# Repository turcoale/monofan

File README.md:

# monofan
PCB de control Fan Monofásico

En este repositorio tengo el control de velocidad de FAN Monofásico.
Fecha de comienzo 23/11/15

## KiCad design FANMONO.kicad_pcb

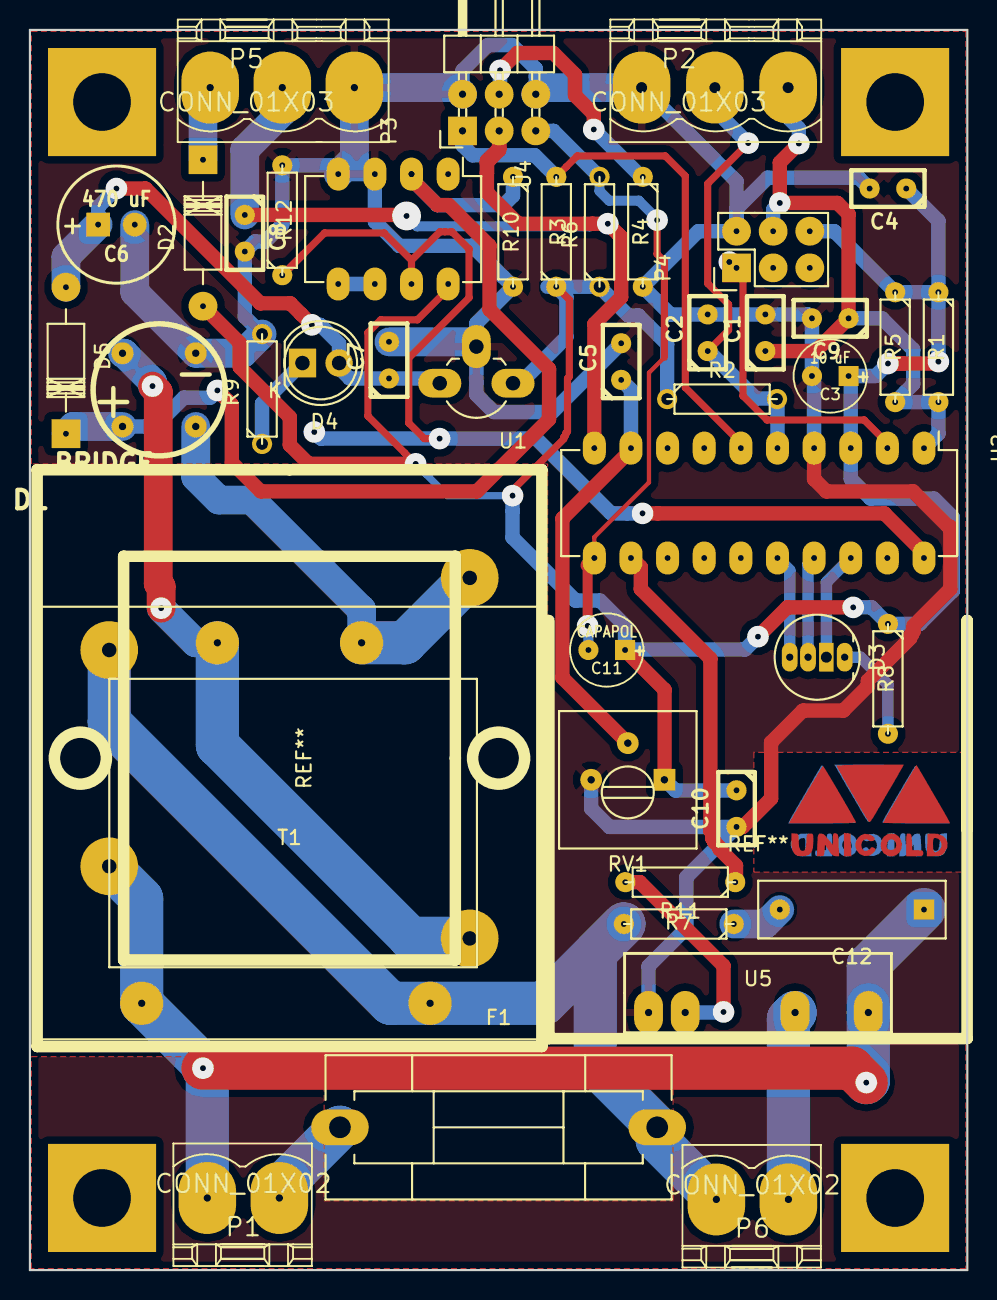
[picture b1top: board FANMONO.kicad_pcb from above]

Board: 2 copper layers, 65.0 x 86.0 mm, 42 parts (0 on the bottom side), 29 nets.

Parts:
C1, C2, C9: 0.1 uF; C1
C3: 10 uF; C1V5
C4, C5, C8: 0,1 uF; C1
C6: 470 uF; C1V8
C7: 0.33 uF; C1
C10: 0.01 uF; C1
C11: CAPAPOL; C1V5
C12: 0.022 uF; C_Rect_L13_W4_P10
D1: BRIDGE; Bridge-rond
D2: 1N4007; Diode_DO-41_SOD81_Horizontal_RM10
D3: Led_RGB_CA; LED-RGB-5MM_Common_Cathode
D4: LED; LED-5MM
D5: DIODE; Diode_DO-41_SOD81_Horizontal_RM10
F1: FUSE; Fuseholder5x20_horiz_SemiClosed_Casing10x25mm
P1, P6: CONN_01X02; PHOENIX_MSTBA2,54-G_2
P2, P5: CONN_01X03; PHOENIX_MSTBA2,54-G_3
P3: JPS; Pin_Header_Angled_2x03
P4: BDM; Pin_Header_Straight_2x03
R1, R2, R3, R4, R5, R6, R10: 10k; R3
R7: 47; R3
R8: 1k; R3
R9: 390; R3
R11: 220; R3
R12: 1 M; R3
RV1: POT; Potentiometer_Trimmer-Suntan-TSR-3386P
T1: TRANSFO; TFCOBSIL2209VCA200mA
U1: 78L05; TO-92_Rugged_Reverse
U2: MC9S08SH8; DIP-20_W7.62mm_LongPads
U4: LM311N; DIP-8_W7.62mm_LongPads
U5: SSR_SHARP; SSR2

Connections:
/AcOut: R11.1, U2.12
/BDM: P4.1, U2.2
/IZC: D1.3, D5.1, R10.1, U4.2
/L: C12.1, P1.2, T1.1, U5.1
/MODE: C11.2, P3.5, R6.2, U2.11
/N: F1.2, P6.2, R7.2, T1.2
/NM: C2.1, P2.2, R2.2, U2.5
/RESET: C1.1, C9.1, P2.3, P4.4, R1.2, R5.2, U2.1
/ST: C5.1, RV1.2, U2.9
/T2: P3.4, R4.1
/ZC: R12.1, U2.20, U4.7
/vreg: C3.1, C4.1, C10.1, C11.1, D2.2, P4.6, R1.1, R2.1, R3.1, R5.1, R6.1, R8.1, RV1.1, U1.1, U2.3, U4.8
GND: C1.2, C2.2, C3.2, C4.2, C5.2, C6.2, C7.2, C8.2, C9.2, C10.2, D1.1, P2.1, P3.2, P3.6, P4.2, P5.3, R4.2, R9.2, R10.2, R12.2, RV1.3, U1.2, U2.4, U4.3, U4.4, U5.4
unnamed: C6.1, C7.1, D4.2, D5.2, U1.3
unnamed: C8.1, P3.3, P5.2, U2.10
unnamed: C12.2, R7.1
unnamed: D1.2, T1.3
unnamed: D1.4, T1.4
unnamed: D2.1, P5.1
unnamed: D3.1, R8.2
unnamed: D3.2, U2.18
unnamed: D3.3, U2.17
unnamed: D3.4, U2.16
unnamed: D4.1, R9.1
unnamed: F1.1, P1.1
unnamed: P3.1, R3.2, U2.6
unnamed: P6.1, U5.2
unnamed: R11.2, U5.3
unnamed: U4.5, U4.6

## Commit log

2015-11-25 agregando carpetas
2015-11-25 carpetas
2015-11-25 prueba desde lenovo
2015-12-02 componentes posicionados
2015-12-03 modificado componente ruteado
2015-12-03 prototipo1.0 enviado a fabricar
2016-01-12 agregando valores de componentes
2016-01-18 realizando firmware
2016-01-26 modificando firmware
2016-02-02 implementado escritura en flash
2016-02-02 Firmware
2016-02-04 modificado el esquematico
2016-02-10 Terminado el ruteo de versión 2.0
2016-02-10 terminada versión 2.0
2016-02-29 commit final febrero
